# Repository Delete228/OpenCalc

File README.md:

Созание opensource калькулятора на основе мк stm32

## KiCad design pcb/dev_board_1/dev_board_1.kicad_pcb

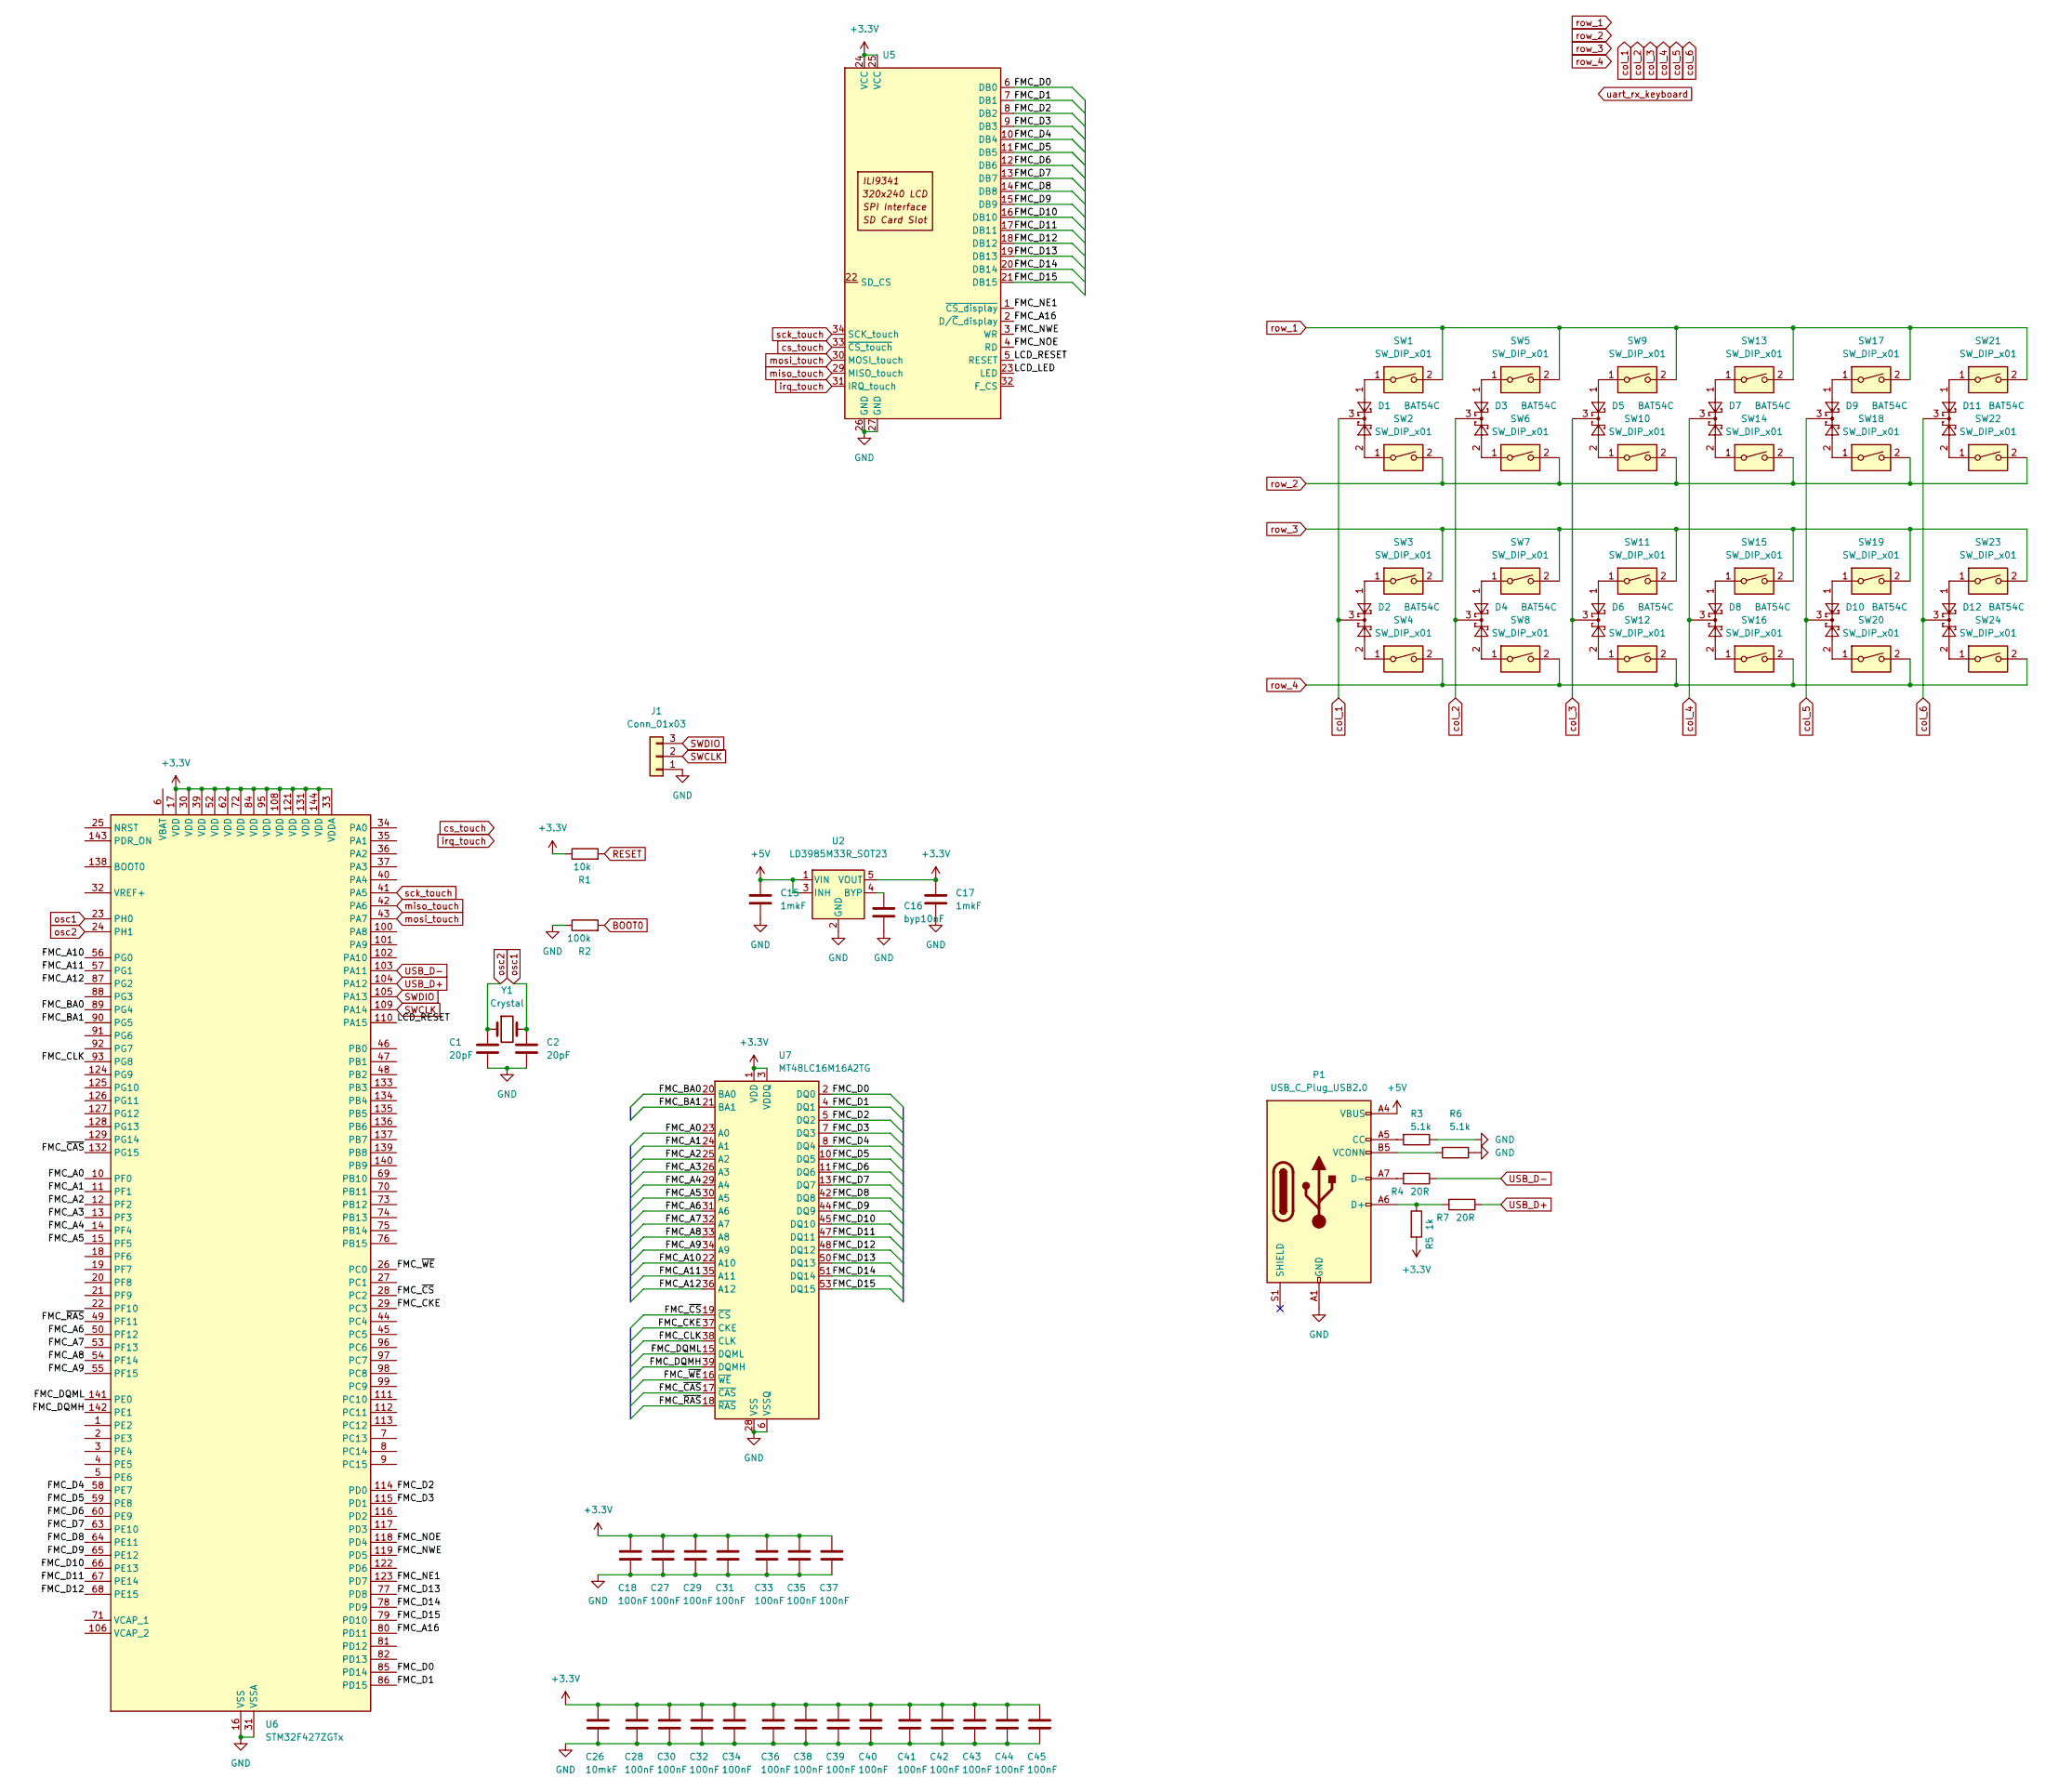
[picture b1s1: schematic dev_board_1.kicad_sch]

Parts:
C1, C2: 20pF; C_0603_1608Metric_Pad1.08x0.95mm_HandSolder
C15, C17: 1mkF; C_0603_1608Metric_Pad1.08x0.95mm_HandSolder
C16: byp10nF; C_0603_1608Metric_Pad1.08x0.95mm_HandSolder
C18, C27, C28, C29, C30, C31, C32, C33, C34, C35, C36, C37, C38, C39, C40, C41, C42, C43, C44, C45: 100nF; C_0603_1608Metric_Pad1.08x0.95mm_HandSolder
C26: 10mkF; C_0603_1608Metric_Pad1.08x0.95mm_HandSolder
D1, D2, D3, D4, D5, D6, D7, D8, D9, D10, D11, D12: BAT54C; SOT-23
J1: Conn_01x03; PinHeader_1x03_P2.54mm_Vertical
P1: USB_C_Plug_USB2.0; USB_C_Receptacle_HRO_TYPE-C-31-M-12
R1: 10k; R_0603_1608Metric_Pad0.98x0.95mm_HandSolder
R2: 100k; R_0603_1608Metric_Pad0.98x0.95mm_HandSolder
R3, R6: 5.1k; R_0603_1608Metric_Pad0.98x0.95mm_HandSolder
R4, R7: 20R; R_0603_1608Metric_Pad0.98x0.95mm_HandSolder
R5: 1k; R_0603_1608Metric_Pad0.98x0.95mm_HandSolder
SW1, SW2, SW3, SW4, SW5, SW6, SW7, SW8, SW9, SW10, SW11, SW12, SW13, SW14, SW15, SW16, SW17, SW18, SW19, SW20, SW21, SW22, SW23, SW24: SW_DIP_x01; SW_SPST_SKQG_WithoutStem
U2: LD3985M33R_SOT23; SOT-23-5
U5: ili9486_16bit_3.2
U6: STM32F427ZGTx; LQFP-144_20x20mm_P0.5mm
U7: MT48LC16M16A2TG; TSOP-II-54_22.2x10.16mm_P0.8mm
Y1: Crystal; Crystal_SMD_2520-4Pin_2.5x2.0mm

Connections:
+3.3V: C17.1, C18.1, C26.1, C27.1, C28.1, C29.1, C30.1, C31.1, C32.1, C33.1, C34.1, C35.1, C36.1, C37.1, C38.1, C39.1, C40.1, C41.1, C42.1, C43.1, C44.1, C45.1, R1.1, R5.2, U2.5 (VOUT), U5.24 (VCC), U5.25 (VCC), U6.17 (VDD), U6.30 (VDD), U6.33 (VDDA), U6.39 (VDD), U6.52 (VDD), U6.62 (VDD), U6.72 (VDD), U6.84 (VDD), U6.95 (VDD), U6.108 (VDD), U6.121 (VDD), U6.131 (VDD), U6.144 (VDD), U7.1 (VDD), U7.3 (VDDQ), U7.9 (VDDQ), U7.14 (VDD), U7.27 (VDD), U7.43 (VDDQ), U7.49 (VDDQ)
+5V: C15.1, P1.A4 (VBUS), P1.A9 (VBUS), P1.B4 (VBUS), P1.B9 (VBUS), U2.1 (VIN), U2.3 (INH)
/FMC_A0: U6.10 (PF0), U7.23 (A0)
/FMC_A1: U6.11 (PF1), U7.24 (A1)
/FMC_A2: U6.12 (PF2), U7.25 (A2)
/FMC_A3: U6.13 (PF3), U7.26 (A3)
/FMC_A4: U6.14 (PF4), U7.29 (A4)
/FMC_A5: U6.15 (PF5), U7.30 (A5)
/FMC_A6: U6.50 (PF12), U7.31 (A6)
/FMC_A7: U6.53 (PF13), U7.32 (A7)
/FMC_A8: U6.54 (PF14), U7.33 (A8)
/FMC_A9: U6.55 (PF15), U7.34 (A9)
/FMC_A10: U6.56 (PG0), U7.22 (A10)
/FMC_A11: U6.57 (PG1), U7.35 (A11)
/FMC_A12: U6.87 (PG2), U7.36 (A12)
/FMC_A16: U5.2 (D/~C_display), U6.80 (PD11)
/FMC_BA0: U6.89 (PG4), U7.20 (BA0)
/FMC_BA1: U6.90 (PG5), U7.21 (BA1)
/FMC_CKE: U6.29 (PC3), U7.37 (CKE)
/FMC_CLK: U6.93 (PG8), U7.38 (CLK)
/FMC_D0: U5.6 (DB0), U6.85 (PD14), U7.2 (DQ0)
/FMC_D1: U5.7 (DB1), U6.86 (PD15), U7.4 (DQ1)
/FMC_D2: U5.8 (DB2), U6.114 (PD0), U7.5 (DQ2)
/FMC_D3: U5.9 (DB3), U6.115 (PD1), U7.7 (DQ3)
/FMC_D4: U5.10 (DB4), U6.58 (PE7), U7.8 (DQ4)
/FMC_D5: U5.11 (DB5), U6.59 (PE8), U7.10 (DQ5)
/FMC_D6: U5.12 (DB6), U6.60 (PE9), U7.11 (DQ6)
/FMC_D7: U5.13 (DB7), U6.63 (PE10), U7.13 (DQ7)
/FMC_D8: U5.14 (DB8), U6.64 (PE11), U7.42 (DQ8)
/FMC_D9: U5.15 (DB9), U6.65 (PE12), U7.44 (DQ9)
/FMC_D10: U5.16 (DB10), U6.66 (PE13), U7.45 (DQ10)
/FMC_D11: U5.17 (DB11), U6.67 (PE14), U7.47 (DQ11)
/FMC_D12: U5.18 (DB12), U6.68 (PE15), U7.48 (DQ12)
/FMC_D13: U5.19 (DB13), U6.77 (PD8), U7.50 (DQ13)
/FMC_D14: U5.20 (DB14), U6.78 (PD9), U7.51 (DQ14)
/FMC_D15: U5.21 (DB15), U6.79 (PD10), U7.53 (DQ15)
/FMC_DQMH: U6.142 (PE1), U7.39 (DQMH)
/FMC_DQML: U6.141 (PE0), U7.15 (DQML)
/FMC_NE1: U5.1 (~CS_display), U6.123 (PD7)
/FMC_NOE: U5.4 (RD), U6.118 (PD4)
/FMC_NWE: U5.3 (WR), U6.119 (PD5)
/FMC_~CAS: U6.132 (PG15), U7.17 (~CAS)
/FMC_~CS: U6.28 (PC2), U7.19 (~CS)
/FMC_~RAS: U6.49 (PF11), U7.18 (~RAS)
/FMC_~WE: U6.26 (PC0), U7.16 (~WE)
/LCD_LED: U5.23 (LED)
/LCD_RESET: U5.5 (RESET), U6.110 (PA15)
BOOT0: R2.2
GND: C1.2, C2.2, C15.2, C16.2, C17.2, C18.2, C26.2, C27.2, C28.2, C29.2, C30.2, C31.2, C32.2, C33.2, C34.2, C35.2, C36.2, C37.2, C38.2, C39.2, C40.2, C41.2, C42.2, C43.2, C44.2, C45.2, J1.1, P1.A1 (GND), P1.A12 (GND), P1.B1 (GND), P1.B12 (GND), R2.1, R3.1, R6.1, U2.2 (GND), U5.26 (GND), U5.27 (GND), U6.16 (VSS), U6.31 (VSSA), U6.38 (VSS), U6.51 (VSS), U6.61 (VSS), U6.83 (VSS), U6.94 (VSS), U6.107 (VSS), U6.120 (VSS), U6.130 (VSS), U7.6 (VSSQ), U7.12 (VSSQ), U7.28 (VSS), U7.41 (VSS), U7.46 (VSSQ), U7.52 (VSSQ), U7.54 (VSS)
unnamed: D1.1, SW1.1
unnamed: D1.2, SW2.1
unnamed: D2.1, SW3.1
unnamed: D2.2, SW4.1
unnamed: D3.1, SW5.1
unnamed: D3.2, SW6.1
unnamed: D4.1, SW7.1
unnamed: D4.2, SW8.1
unnamed: D5.1, SW9.1
unnamed: D5.2, SW10.1
unnamed: D6.1, SW11.1
unnamed: D6.2, SW12.1
unnamed: D7.1, SW13.1
unnamed: D7.2, SW14.1
unnamed: D8.1, SW15.1
unnamed: D8.2, SW16.1
unnamed: D9.1, SW17.1
unnamed: D9.2, SW18.1
unnamed: D10.1, SW19.1
unnamed: D10.2, SW20.1
unnamed: D11.1, SW21.1
unnamed: D11.2, SW22.1
unnamed: D12.1, SW23.1
unnamed: D12.2, SW24.1
unnamed: P1.A5 (CC), R3.2
unnamed: P1.A6 (D+), R5.1, R7.2
unnamed: P1.A7 (D-), R4.2
unnamed: P1.B5 (VCONN), R6.2
unnamed: C16.1, U2.4 (BYP)
RESET: R1.2
SWCLK: J1.2, U6.109 (PA14)
SWDIO: J1.3, U6.105 (PA13)
USB_D+: R7.1, U6.104 (PA12)
USB_D-: R4.1, U6.103 (PA11)
col_1: D1.3, D2.3
col_2: D3.3, D4.3
col_3: D5.3, D6.3
col_4: D7.3, D8.3
col_5: D9.3, D10.3
col_6: D11.3, D12.3
cs_touch: U5.33 (~CS_touch)
irq_touch: U5.31 (IRQ_touch)
miso_touch: U5.29 (MISO_touch), U6.42 (PA6)
mosi_touch: U5.30 (MOSI_touch), U6.43 (PA7)
osc1: C2.1, U6.23 (PH0), Y1.2
osc2: C1.1, U6.24 (PH1), Y1.1
row_1: SW1.2, SW5.2, SW9.2, SW13.2, SW17.2, SW21.2
row_2: SW2.2, SW6.2, SW10.2, SW14.2, SW18.2, SW22.2
row_3: SW3.2, SW7.2, SW11.2, SW15.2, SW19.2, SW23.2
row_4: SW4.2, SW8.2, SW12.2, SW16.2, SW20.2, SW24.2
sck_touch: U5.34 (SCK_touch), U6.41 (PA5)

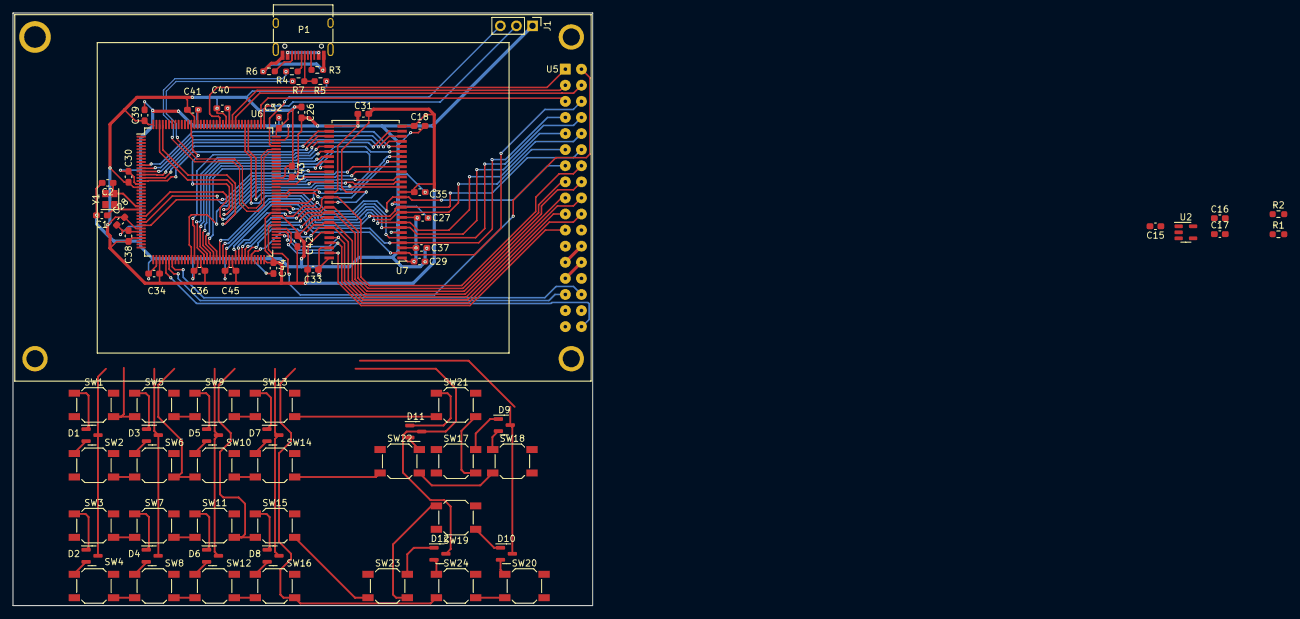
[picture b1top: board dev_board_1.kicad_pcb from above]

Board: 2 copper layers, 91.5 x 93.5 mm, 76 parts (0 on the bottom side), 95 nets.

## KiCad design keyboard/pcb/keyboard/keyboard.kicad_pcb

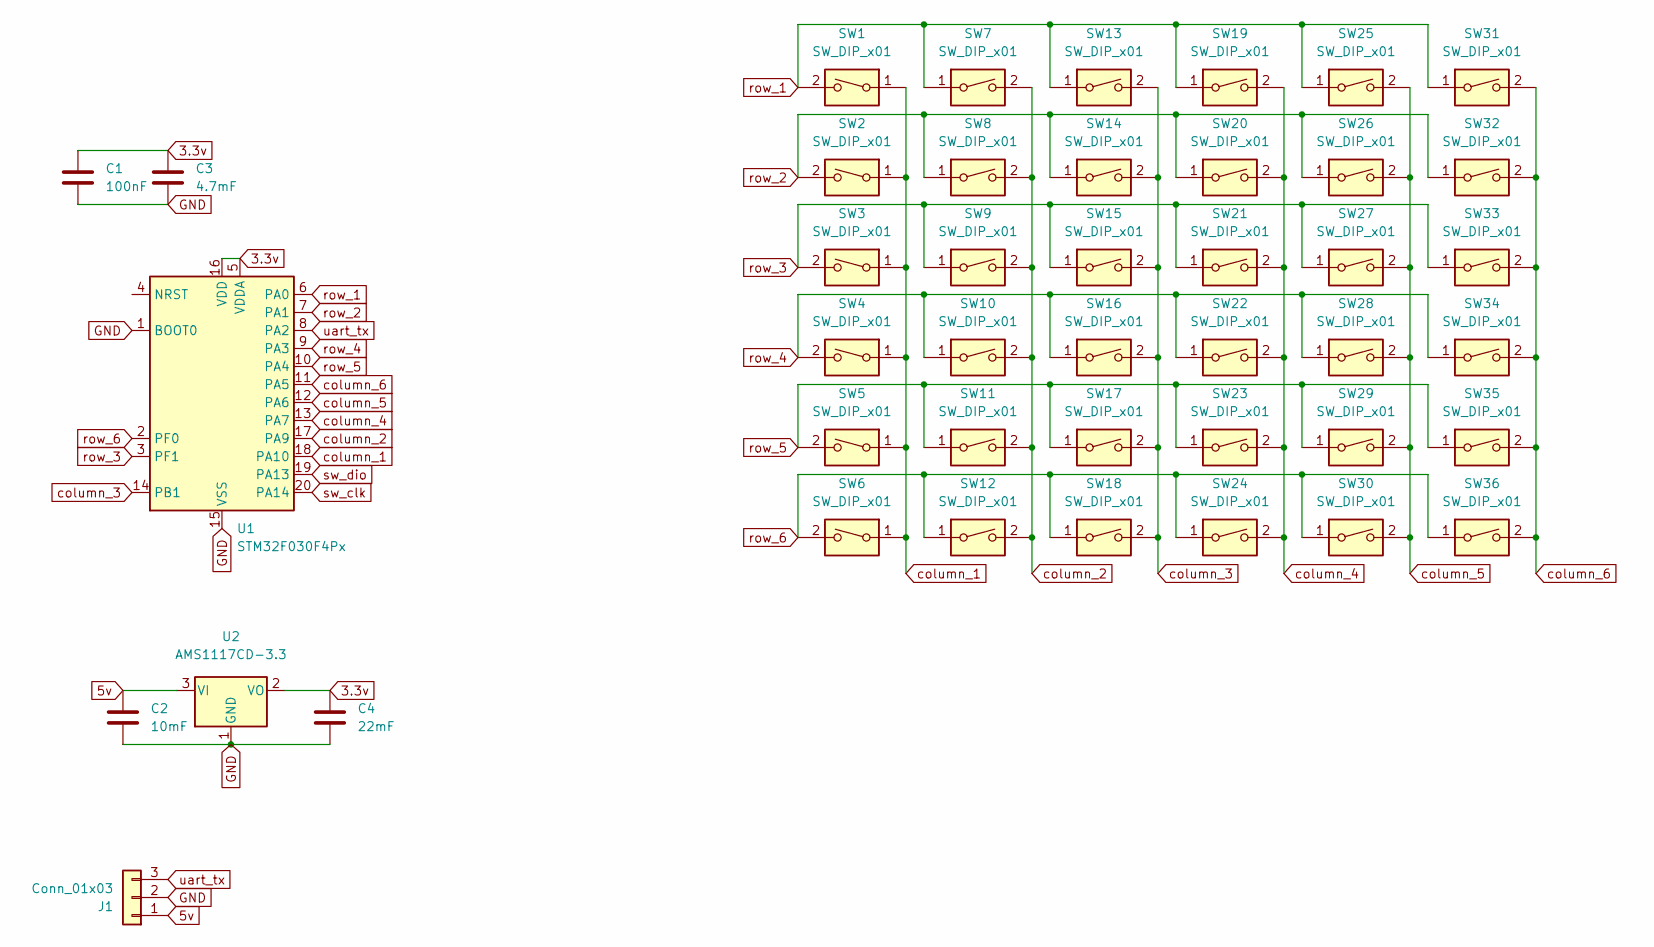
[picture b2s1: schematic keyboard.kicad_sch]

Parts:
C1: 100nF; C_0805_2012Metric_Pad1.18x1.45mm_HandSolder
C2: 10mF; C_0805_2012Metric_Pad1.18x1.45mm_HandSolder
C3: 4.7mF; C_0805_2012Metric_Pad1.18x1.45mm_HandSolder
C4: 22mF; C_0805_2012Metric_Pad1.18x1.45mm_HandSolder
J1: Conn_01x03; PinSocket_1x03_P2.54mm_Vertical
SW1, SW2, SW3, SW4, SW5, SW6, SW7, SW8, SW9, SW10, SW11, SW12, SW13, SW14, SW15, SW16, SW17, SW18, SW19, SW20, SW21, SW22, SW23, SW24, SW25, SW26, SW27, SW28, SW29, SW30, SW31, SW32, SW33, SW34, SW35, SW36: SW_DIP_x01; btn_8x8
U1: STM32F030F4Px; TSSOP-20_4.4x6.5mm_P0.65mm
U2: AMS1117CD-3.3; TO-252-3_TabPin2

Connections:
3.3v: C1.1, C3.1, C4.1, U1.5 (VDDA), U1.16 (VDD), U2.2 (VO)
5v: C2.1, J1.1, U2.3 (VI)
GND: C1.2, C2.2, C3.2, C4.2, J1.2, U1.1 (BOOT0), U1.15 (VSS), U2.1 (GND)
column_1: SW1.1, SW2.1, SW3.1, SW4.1, SW5.1, SW6.1, U1.18 (PA10)
column_2: SW7.2, SW8.2, SW9.2, SW10.2, SW11.2, SW12.2, U1.17 (PA9)
column_3: SW13.2, SW14.2, SW15.2, SW16.2, SW17.2, SW18.2, U1.14 (PB1)
column_4: SW19.2, SW20.2, SW21.2, SW22.2, SW23.2, SW24.2, U1.13 (PA7)
column_5: SW25.2, SW26.2, SW27.2, SW28.2, SW29.2, SW30.2, U1.12 (PA6)
column_6: SW31.2, SW32.2, SW33.2, SW34.2, SW35.2, SW36.2, U1.11 (PA5)
row_1: SW1.2, SW7.1, SW13.1, SW19.1, SW25.1, SW31.1, U1.6 (PA0)
row_2: SW2.2, SW8.1, SW14.1, SW20.1, SW26.1, SW32.1, U1.7 (PA1)
row_3: SW3.2, SW9.1, SW15.1, SW21.1, SW27.1, SW33.1, U1.3 (PF1)
row_4: SW4.2, SW10.1, SW16.1, SW22.1, SW28.1, SW34.1, U1.9 (PA3)
row_5: SW5.2, SW11.1, SW17.1, SW23.1, SW29.1, SW35.1, U1.10 (PA4)
row_6: SW6.2, SW12.1, SW18.1, SW24.1, SW30.1, SW36.1, U1.2 (PF0)
sw_clk: U1.20 (PA14)
sw_dio: U1.19 (PA13)
uart_tx: J1.3, U1.8 (PA2)

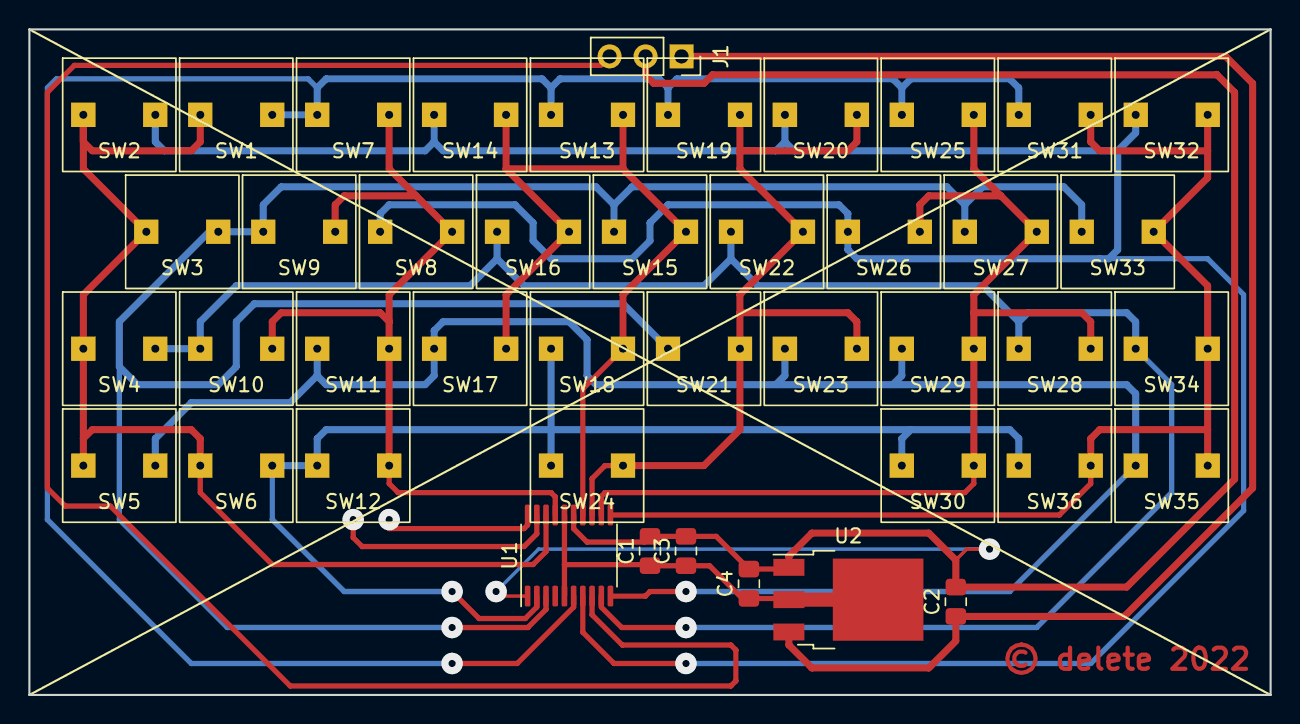
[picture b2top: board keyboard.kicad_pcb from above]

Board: 2 copper layers, 87.6 x 47.0 mm, 43 parts (0 on the bottom side), 16 nets.

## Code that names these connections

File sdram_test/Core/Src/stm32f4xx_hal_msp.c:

/* USER CODE BEGIN Header */
/**
  ******************************************************************************
  * @file         stm32f4xx_hal_msp.c
  * @brief        This file provides code for the MSP Initialization
  *               and de-Initialization codes.
  ******************************************************************************
  * @attention
  *
  * Copyright (c) 2023 STMicroelectronics.
  * All rights reserved.
  *
  * This software is licensed under terms that can be found in the LICENSE file
  * in the root directory of this software component.
  * If no LICENSE file comes with this software, it is provided AS-IS.
  *
  ******************************************************************************
  */
/* USER CODE END Header */

/* Includes ------------------------------------------------------------------*/
#include "main.h"

/* USER CODE BEGIN Includes */

/* USER CODE END Includes */

/* Private typedef -----------------------------------------------------------*/
/* USER CODE BEGIN TD */

/* USER CODE END TD */

/* Private define ------------------------------------------------------------*/
/* USER CODE BEGIN Define */

/* USER CODE END Define */

/* Private macro -------------------------------------------------------------*/
/* USER CODE BEGIN Macro */

/* USER CODE END Macro */

/* Private variables ---------------------------------------------------------*/
/* USER CODE BEGIN PV */

/* USER CODE END PV */

/* Private function prototypes -----------------------------------------------*/
/* USER CODE BEGIN PFP */

/* USER CODE END PFP */

/* External functions --------------------------------------------------------*/
/* USER CODE BEGIN ExternalFunctions */

/* USER CODE END ExternalFunctions */

/* USER CODE BEGIN 0 */

/* USER CODE END 0 */
/**
  * Initializes the Global MSP.
  */
void HAL_MspInit(void)
{
  /* USER CODE BEGIN MspInit 0 */

  /* USER CODE END MspInit 0 */

  __HAL_RCC_SYSCFG_CLK_ENABLE();
  __HAL_RCC_PWR_CLK_ENABLE();

  /* System interrupt init*/

  /* USER CODE BEGIN MspInit 1 */

  /* USER CODE END MspInit 1 */
}

static uint32_t FMC_Initialized = 0;

static void HAL_FMC_MspInit(void){
  /* USER CODE BEGIN FMC_MspInit 0 */

  /* USER CODE END FMC_MspInit 0 */
  GPIO_InitTypeDef GPIO_InitStruct ={0};
  if (FMC_Initialized) {
    return;
  }
  FMC_Initialized = 1;

  /* Peripheral clock enable */
  __HAL_RCC_FMC_CLK_ENABLE();

  /** FMC GPIO Configuration
  PF0   ------> FMC_A0
  PF1   ------> FMC_A1
  PF2   ------> FMC_A2
  PF3   ------> FMC_A3
  PF4   ------> FMC_A4
  PF5   ------> FMC_A5
  PC0   ------> FMC_SDNWE
  PC2   ------> FMC_SDNE0
  PC3   ------> FMC_SDCKE0
  PF11   ------> FMC_SDNRAS
  PF12   ------> FMC_A6
  PF13   ------> FMC_A7
  PF14   ------> FMC_A8
  PF15   ------> FMC_A9
  PG0   ------> FMC_A10
  PG1   ------> FMC_A11
  PE7   ------> FMC_D4
  PE8   ------> FMC_D5
  PE9   ------> FMC_D6
  PE10   ------> FMC_D7
  PE11   ------> FMC_D8
  PE12   ------> FMC_D9
  PE13   ------> FMC_D10
  PE14   ------> FMC_D11
  PE15   ------> FMC_D12
  PD8   ------> FMC_D13
  PD9   ------> FMC_D14
  PD10   ------> FMC_D15
  PD14   ------> FMC_D0
  PD15   ------> FMC_D1
  PG2   ------> FMC_A12
  PG4   ------> FMC_BA0
  PG5   ------> FMC_BA1
  PG8   ------> FMC_SDCLK
  PD0   ------> FMC_D2
  PD1   ------> FMC_D3
  PG15   ------> FMC_SDNCAS
  */
  GPIO_InitStruct.Pin = GPIO_PIN_0|GPIO_PIN_1|GPIO_PIN_2|GPIO_PIN_3
                          |GPIO_PIN_4|GPIO_PIN_5|GPIO_PIN_11|GPIO_PIN_12
                          |GPIO_PIN_13|GPIO_PIN_14|GPIO_PIN_15;
  GPIO_InitStruct.Mode = GPIO_MODE_AF_PP;
  GPIO_InitStruct.Pull = GPIO_NOPULL;
  GPIO_InitStruct.Speed = GPIO_SPEED_FREQ_VERY_HIGH;
  GPIO_InitStruct.Alternate = GPIO_AF12_FMC;
  HAL_GPIO_Init(GPIOF, &GPIO_InitStruct);

  GPIO_InitStruct.Pin = GPIO_PIN_0|GPIO_PIN_2|GPIO_PIN_3;
  GPIO_InitStruct.Mode = GPIO_MODE_AF_PP;
  GPIO_InitStruct.Pull = GPIO_NOPULL;
  GPIO_InitStruct.Speed = GPIO_SPEED_FREQ_VERY_HIGH;
  GPIO_InitStruct.Alternate = GPIO_AF12_FMC;
  HAL_GPIO_Init(GPIOC, &GPIO_InitStruct);

  GPIO_InitStruct.Pin = GPIO_PIN_0|GPIO_PIN_1|GPIO_PIN_2|GPIO_PIN_4
                          |GPIO_PIN_5|GPIO_PIN_8|GPIO_PIN_15;
  GPIO_InitStruct.Mode = GPIO_MODE_AF_PP;
  GPIO_InitStruct.Pull = GPIO_NOPULL;
  GPIO_InitStruct.Speed = GPIO_SPEED_FREQ_VERY_HIGH;
  GPIO_InitStruct.Alternate = GPIO_AF12_FMC;
  HAL_GPIO_Init(GPIOG, &GPIO_InitStruct);

  GPIO_InitStruct.Pin = GPIO_PIN_7|GPIO_PIN_8|GPIO_PIN_9|GPIO_PIN_10
                          |GPIO_PIN_11|GPIO_PIN_12|GPIO_PIN_13|GPIO_PIN_14
                          |GPIO_PIN_15;
  GPIO_InitStruct.Mode = GPIO_MODE_AF_PP;
  GPIO_InitStruct.Pull = GPIO_NOPULL;
  GPIO_InitStruct.Speed = GPIO_SPEED_FREQ_VERY_HIGH;
  GPIO_InitStruct.Alternate = GPIO_AF12_FMC;
  HAL_GPIO_Init(GPIOE, &GPIO_InitStruct);

  GPIO_InitStruct.Pin = GPIO_PIN_8|GPIO_PIN_9|GPIO_PIN_10|GPIO_PIN_14
                          |GPIO_PIN_15|GPIO_PIN_0|GPIO_PIN_1;
  GPIO_InitStruct.Mode = GPIO_MODE_AF_PP;
  GPIO_InitStruct.Pull = GPIO_NOPULL;
  GPIO_InitStruct.Speed = GPIO_SPEED_FREQ_VERY_HIGH;
  GPIO_InitStruct.Alternate = GPIO_AF12_FMC;
  HAL_GPIO_Init(GPIOD, &GPIO_InitStruct);

  /* USER CODE BEGIN FMC_MspInit 1 */

  /* USER CODE END FMC_MspInit 1 */
}

void HAL_SDRAM_MspInit(SDRAM_HandleTypeDef* hsdram){
  /* USER CODE BEGIN SDRAM_MspInit 0 */

  /* USER CODE END SDRAM_MspInit 0 */
  HAL_FMC_MspInit();
  /* USER CODE BEGIN SDRAM_MspInit 1 */

  /* USER CODE END SDRAM_MspInit 1 */
}

static uint32_t FMC_DeInitialized = 0;

static void HAL_FMC_MspDeInit(void){
  /* USER CODE BEGIN FMC_MspDeInit 0 */

  /* USER CODE END FMC_MspDeInit 0 */
  if (FMC_DeInitialized) {
    return;
  }
  FMC_DeInitialized = 1;
  /* Peripheral clock enable */
  __HAL_RCC_FMC_CLK_DISABLE();

  /** FMC GPIO Configuration
  PF0   ------> FMC_A0
  PF1   ------> FMC_A1
  PF2   ------> FMC_A2
  PF3   ------> FMC_A3
  PF4   ------> FMC_A4
  PF5   ------> FMC_A5
  PC0   ------> FMC_SDNWE
  PC2   ------> FMC_SDNE0
  PC3   ------> FMC_SDCKE0
  PF11   ------> FMC_SDNRAS
  PF12   ------> FMC_A6
  PF13   ------> FMC_A7
  PF14   ------> FMC_A8
  PF15   ------> FMC_A9
  PG0   ------> FMC_A10
  PG1   ------> FMC_A11
  PE7   ------> FMC_D4
  PE8   ------> FMC_D5
  PE9   ------> FMC_D6
  PE10   ------> FMC_D7
  PE11   ------> FMC_D8
  PE12   ------> FMC_D9
  PE13   ------> FMC_D10
  PE14   ------> FMC_D11
  PE15   ------> FMC_D12
  PD8   ------> FMC_D13
  PD9   ------> FMC_D14
  PD10   ------> FMC_D15
  PD14   ------> FMC_D0
  PD15   ------> FMC_D1
  PG2   ------> FMC_A12
  PG4   ------> FMC_BA0
  PG5   ------> FMC_BA1
  PG8   ------> FMC_SDCLK
  PD0   ------> FMC_D2
  PD1   ------> FMC_D3
  PG15   ------> FMC_SDNCAS
  */
  HAL_GPIO_DeInit(GPIOF, GPIO_PIN_0|GPIO_PIN_1|GPIO_PIN_2|GPIO_PIN_3
                          |GPIO_PIN_4|GPIO_PIN_5|GPIO_PIN_11|GPIO_PIN_12
                          |GPIO_PIN_13|GPIO_PIN_14|GPIO_PIN_15);

  HAL_GPIO_DeInit(GPIOC, GPIO_PIN_0|GPIO_PIN_2|GPIO_PIN_3);

  HAL_GPIO_DeInit(GPIOG, GPIO_PIN_0|GPIO_PIN_1|GPIO_PIN_2|GPIO_PIN_4
                          |GPIO_PIN_5|GPIO_PIN_8|GPIO_PIN_15);

  HAL_GPIO_DeInit(GPIOE, GPIO_PIN_7|GPIO_PIN_8|GPIO_PIN_9|GPIO_PIN_10
                          |GPIO_PIN_11|GPIO_PIN_12|GPIO_PIN_13|GPIO_PIN_14
                          |GPIO_PIN_15);

  HAL_GPIO_DeInit(GPIOD, GPIO_PIN_8|GPIO_PIN_9|GPIO_PIN_10|GPIO_PIN_14
                          |GPIO_PIN_15|GPIO_PIN_0|GPIO_PIN_1);

  /* USER CODE BEGIN FMC_MspDeInit 1 */

  /* USER CODE END FMC_MspDeInit 1 */
}

void HAL_SDRAM_MspDeInit(SDRAM_HandleTypeDef* hsdram){
  /* USER CODE BEGIN SDRAM_MspDeInit 0 */

  /* USER CODE END SDRAM_MspDeInit 0 */
  HAL_FMC_MspDeInit();
  /* USER CODE BEGIN SDRAM_MspDeInit 1 */

  /* USER CODE END SDRAM_MspDeInit 1 */
}

/* USER CODE BEGIN 1 */

/* USER CODE END 1 */

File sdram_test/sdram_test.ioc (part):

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Mcu.Name=STM32F427Z(G-I)Tx
Mcu.Package=LQFP144
Mcu.UserName=STM32F427ZGTx
PA11.Mode=Device_Only
PA11.Signal=USB_OTG_FS_DM
PA12.Mode=Device_Only
PA12.Signal=USB_OTG_FS_DP
PA13.Mode=Serial_Wire
PA13.Signal=SYS_JTMS-SWDIO
PA14.Mode=Serial_Wire
PA14.Signal=SYS_JTCK-SWCLK
PA5.Mode=Full_Duplex_Master
PA5.Signal=SPI1_SCK
PA6.Mode=Full_Duplex_Master
PA6.Signal=SPI1_MISO
PA7.Mode=Full_Duplex_Master
PA7.Signal=SPI1_MOSI
PC0.Signal=FMC_SDNWE
PC2.Mode=SdramChipSelect1_1
PC2.Signal=FMC_SDNE0
PC3.Mode=SdramChipSelect1_1
PC3.Signal=FMC_SDCKE0
PD0.Signal=FMC_D2_DA2
PD1.Signal=FMC_D3_DA3
PD10.Signal=FMC_D15_DA15
PD11.Signal=FMC_A16_CLE
PD14.Signal=FMC_D0_DA0
PD15.Signal=FMC_D1_DA1
PD4.Signal=FMC_NOE
PD5.Signal=FMC_NWE
PD7.Mode=NorPsramChipSelect1_1
PD7.Signal=FMC_NE1
PD8.Signal=FMC_D13_DA13
PD9.Signal=FMC_D14_DA14
PE0.Signal=FMC_NBL0
PE1.Signal=FMC_NBL1
PE10.Signal=FMC_D7_DA7
PE11.Signal=FMC_D8_DA8
PE12.Signal=FMC_D9_DA9
PE13.Signal=FMC_D10_DA10
PE14.Signal=FMC_D11_DA11
PE15.Signal=FMC_D12_DA12
PE7.Signal=FMC_D4_DA4
PE8.Signal=FMC_D5_DA5
PE9.Signal=FMC_D6_DA6
PF0.Signal=FMC_A0
PF1.Signal=FMC_A1
PF11.Signal=FMC_SDNRAS
PF12.Signal=FMC_A6
PF13.Signal=FMC_A7
PF14.Signal=FMC_A8
PF15.Signal=FMC_A9
PF2.Signal=FMC_A2
PF3.Signal=FMC_A3
PF4.Signal=FMC_A4
PF5.Signal=FMC_A5
PG0.Signal=FMC_A10
PG1.Signal=FMC_A11
PG15.Signal=FMC_SDNCAS
PG2.Signal=FMC_A12
PG4.Signal=FMC_A14_BA0
PG5.Signal=FMC_A15_BA1
PG8.Signal=FMC_SDCLK
PH0/OSC_IN.Mode=HSE-External-Oscillator
PH0/OSC_IN.Signal=RCC_OSC_IN
PH1/OSC_OUT.Mode=HSE-External-Oscillator
PH1/OSC_OUT.Signal=RCC_OSC_OUT
RCC.HSE_VALUE=8000000
RCC.SYSCLKFreq_VALUE=180000000
RCC.SYSCLKSource=RCC_SYSCLKSOURCE_PLLCLK
board=custom

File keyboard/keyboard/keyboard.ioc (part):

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Mcu.Name=STM32F030F4Px
Mcu.Package=TSSOP20
Mcu.UserName=STM32F030F4Px
PA0.GPIOParameters=GPIO_Label
PA0.GPIO_Label=row_1
PA0.Signal=GPIO_Output
PA1.GPIOParameters=GPIO_Label
PA1.GPIO_Label=row_2
PA1.Signal=GPIO_Output
PA10.GPIOParameters=GPIO_PuPd,GPIO_Label
PA10.GPIO_Label=colunm_1
PA10.GPIO_PuPd=GPIO_PULLDOWN
PA10.Signal=GPIO_Input
PA13.Mode=Serial_Wire
PA13.Signal=SYS_SWDIO
PA14.Mode=Serial_Wire
PA14.Signal=SYS_SWCLK
PA2.Mode=Half_duplex(single_wire_mode)
PA2.Signal=USART1_TX
PA3.GPIOParameters=GPIO_Label
PA3.GPIO_Label=row_3
PA3.Signal=GPIO_Output
PA4.GPIOParameters=GPIO_Label
PA4.GPIO_Label=row_4
PA4.Signal=GPIO_Output
PA5.GPIOParameters=GPIO_PuPd,GPIO_Label
PA5.GPIO_Label=colunm_6
PA5.GPIO_PuPd=GPIO_PULLDOWN
PA5.Signal=GPIO_Input
PA6.GPIOParameters=GPIO_PuPd,GPIO_Label
PA6.GPIO_Label=colunm_5
PA6.GPIO_PuPd=GPIO_PULLDOWN
PA6.Signal=GPIO_Input
PA7.GPIOParameters=GPIO_PuPd,GPIO_Label
PA7.GPIO_Label=colunm_4
PA7.GPIO_PuPd=GPIO_PULLDOWN
PA7.Signal=GPIO_Input
PA9.GPIOParameters=GPIO_PuPd,GPIO_Label
PA9.GPIO_Label=colunm_2
PA9.GPIO_PuPd=GPIO_PULLDOWN
PA9.Signal=GPIO_Input
PB1.GPIOParameters=GPIO_PuPd,GPIO_Label
PB1.GPIO_Label=colunm_3
PB1.GPIO_PuPd=GPIO_PULLDOWN
PB1.Signal=GPIO_Input
PF0-OSC_IN.GPIOParameters=GPIO_Label
PF0-OSC_IN.GPIO_Label=row_5
PF0-OSC_IN.Signal=GPIO_Output
PF1-OSC_OUT.GPIOParameters=GPIO_Label
PF1-OSC_OUT.GPIO_Label=row_6
PF1-OSC_OUT.Signal=GPIO_Output
RCC.SYSCLKFreq_VALUE=48000000
RCC.SYSCLKSource=RCC_SYSCLKSOURCE_PLLCLK
board=custom

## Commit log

2022-03-28 Add readme
2022-03-31 Update keyboard pcd
2022-04-01 Add power supply to keyboard scheme
2022-04-01 Some fix keyboard scheme
2022-04-01 Add copyright to keyboard scheme
2022-04-01 75% one layer
2023-09-13 gitignore
2023-09-25 start develop calc board whith sdram
    Start developing new board? whith sdram and 144LQFT stm32
2023-09-26 add display
    Add ili9341 display whit parallel interface
2023-09-26 New buttons for calc keyboard
2023-09-26 add another trace for sdram
2023-09-27 change pcb_libs settings
2023-10-16 playing whith topor
2023-10-16 add track to display and usb c
2023-10-16 place buttons

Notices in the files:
keyboard/pcb/keyboard/keyboard.kicad_pcb:
© delete 2022
